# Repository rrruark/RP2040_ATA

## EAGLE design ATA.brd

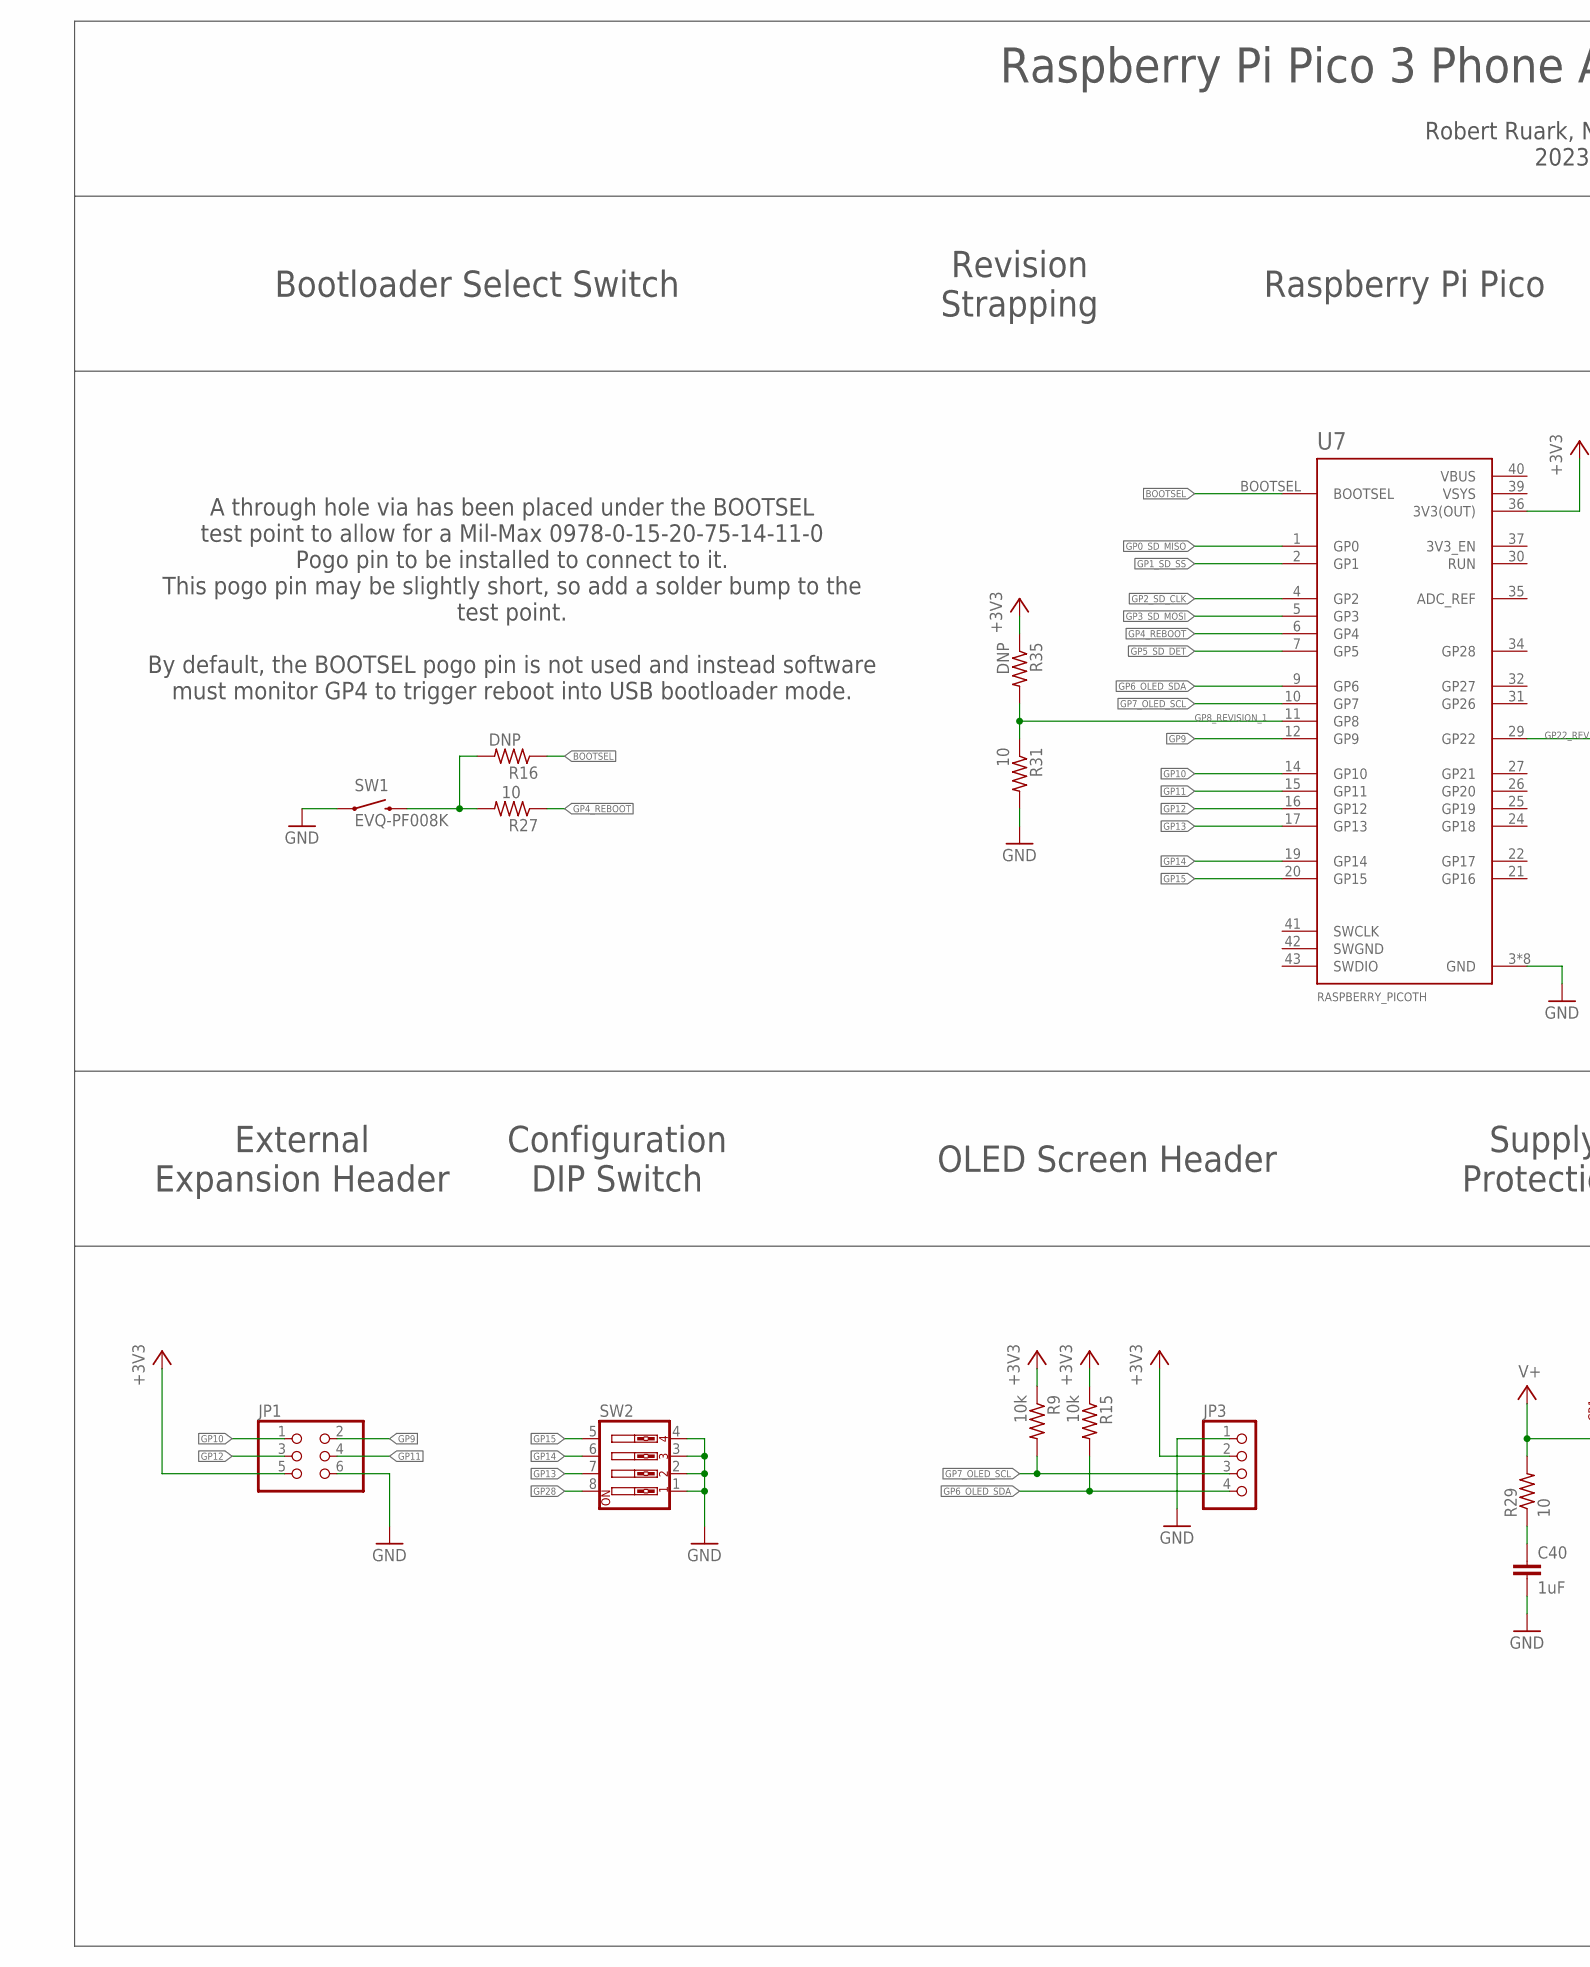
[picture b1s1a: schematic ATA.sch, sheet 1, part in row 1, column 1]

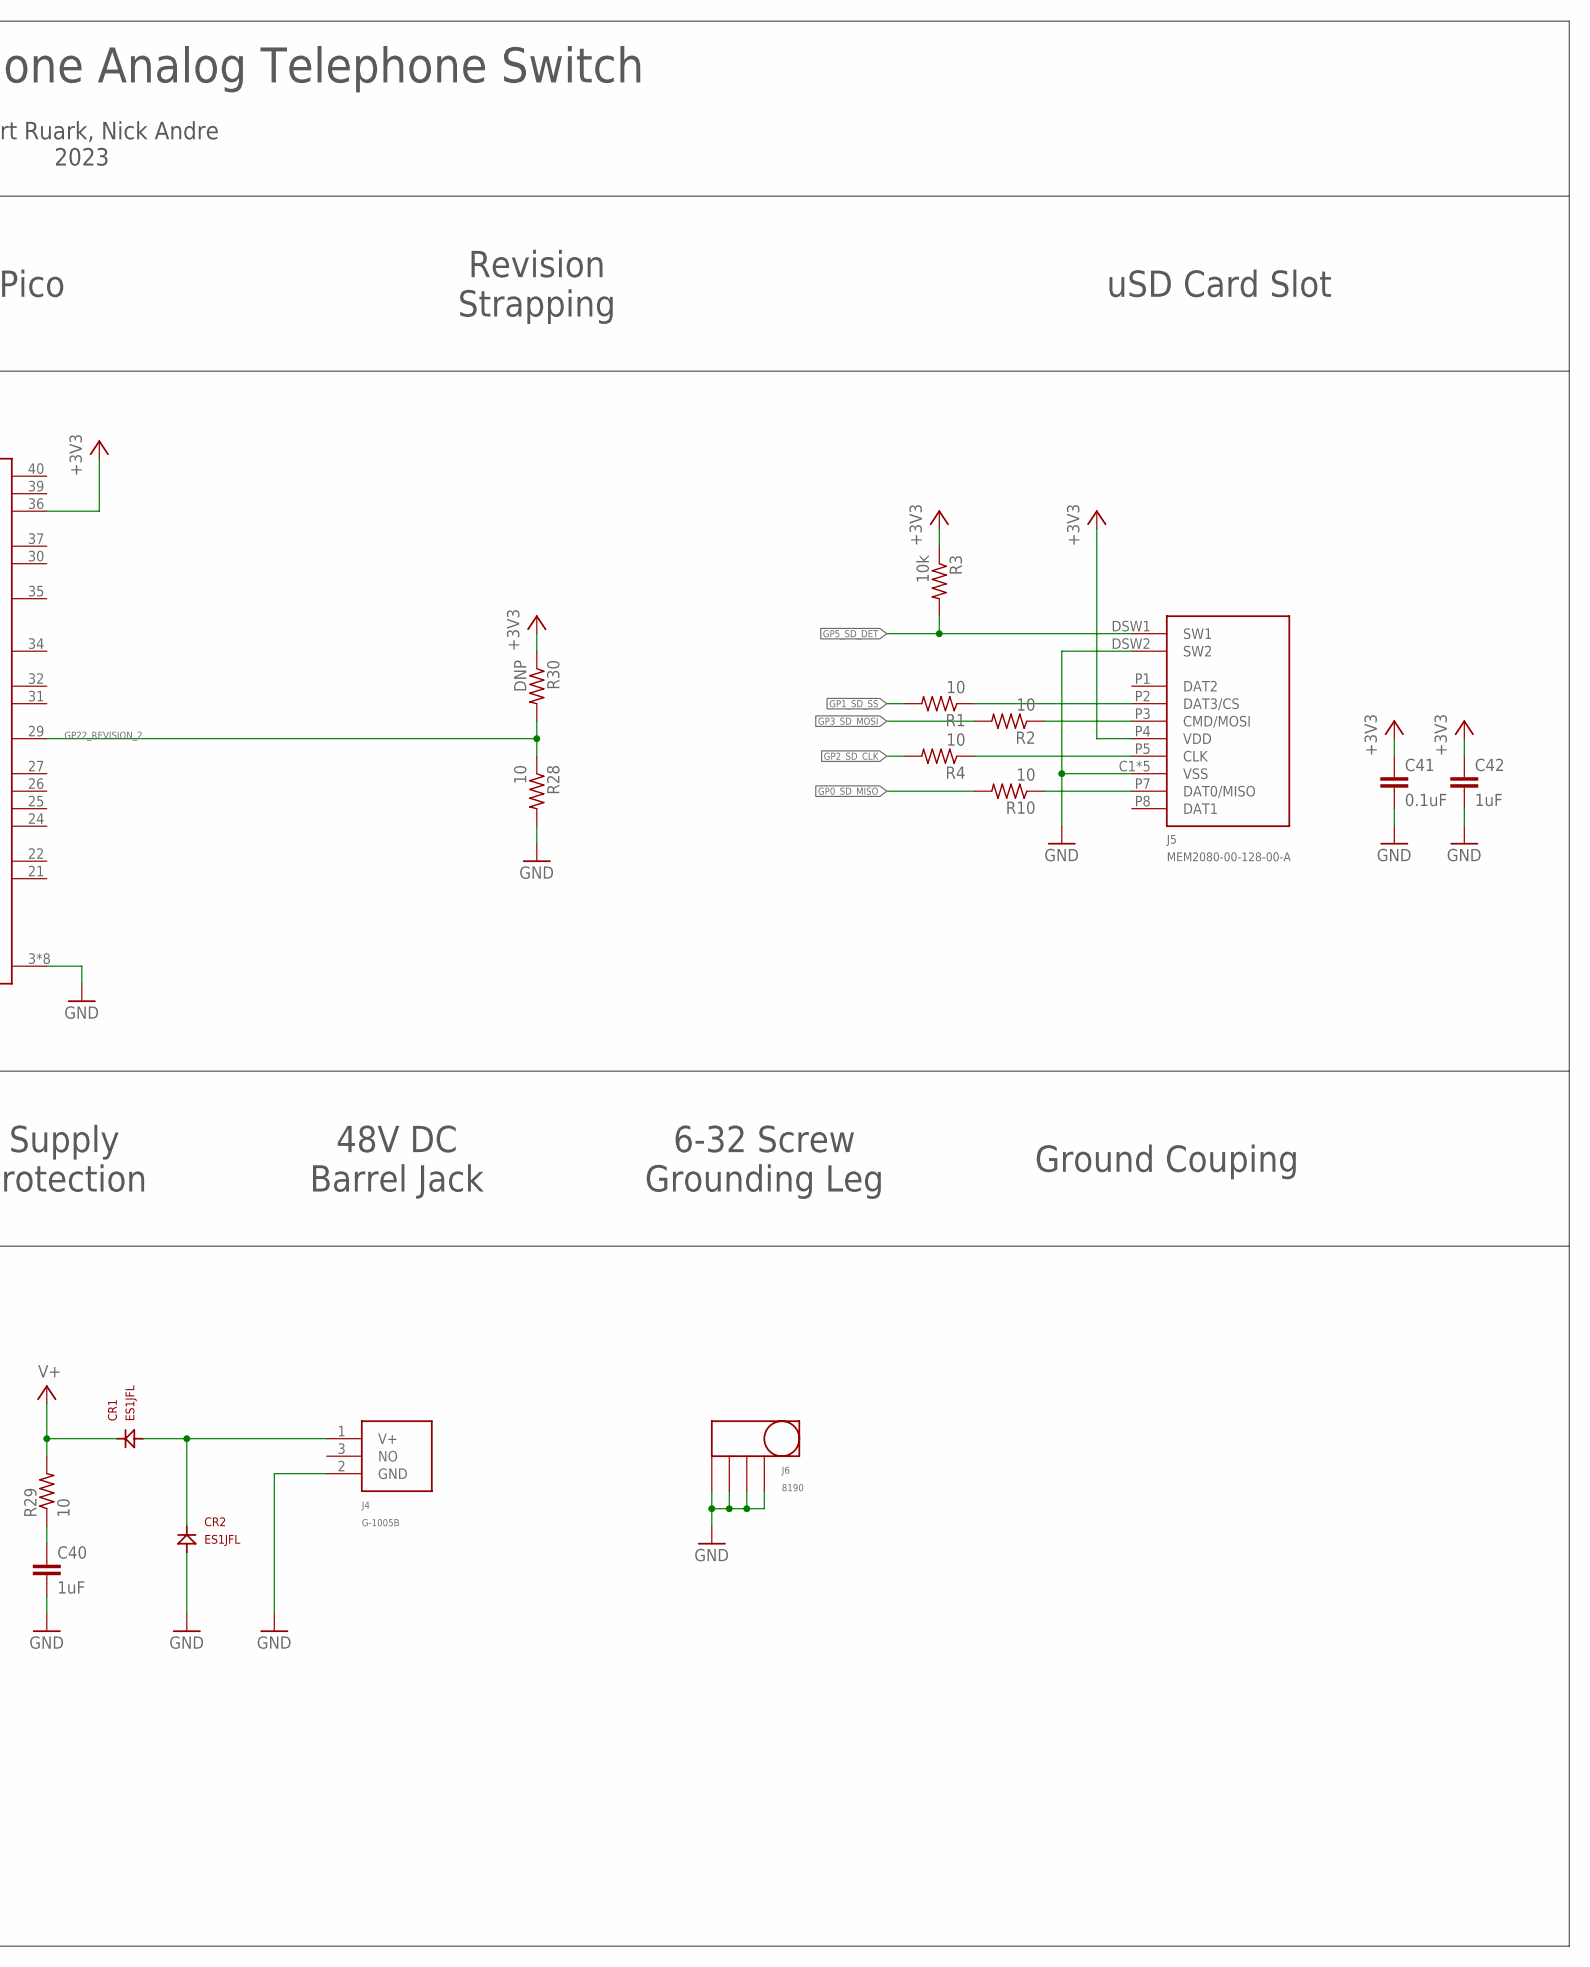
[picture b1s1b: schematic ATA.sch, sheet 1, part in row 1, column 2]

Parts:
C40: 1uF; 1206
C41: 0.1uF; 0603
C42: 1uF; 0805
CR1, CR2: ES1JFL; SOD123(AK)
J4: G-1005B
J5: MEM2080-00-128-00-A; MEM2080
J6: 8190; 7781
JP1: PINHD-2X3/90; 2X03/90
JP3: PINHD-1X4; 1X04
R1, R2, R4, R10, R27, R28, R31: 10; 0603
R3, R9, R15: 10k; 0603
R16, R30, R35: DNP; 0603
R29: 10; 1206
SW1: EVQ-PF008K
SW2: SW_DIP-4; EDG-04
U7: RASPBERRY_PICOTH; PICO-PKG-TH

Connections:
+3V3: C41.1, C42.1, J5.P4 (VDD), JP1.5, JP3.2, R3.1, R9.1, R15.1, R30.1, R35.1, U7.36 (3V3(OUT))
BOOTSEL: R16.1, U7.BOOTSEL
GND: C40.2, C41.2, C42.2, CR2.A, J4.2 (GND), J5.C1 (VSS), J5.C2 (VSS), J5.C3 (VSS), J5.C4 (VSS), J5.DSW2 (SW2), J5.P6 (VSS), J6.P$1, J6.P$2, J6.P$3, J6.P$4, JP1.6, JP3.1, R28.2, R31.2, SW1.S1 (1), SW2.1, SW2.2, SW2.3, SW2.4, U7.3 (GND), U7.8 (GND), U7.13 (GND), U7.18 (GND), U7.23 (GND), U7.28 (GND), U7.33 (GND), U7.38 (GND); also elsewhere on the board
GP0_SD_MISO: R10.2, U7.1 (GP0)
GP1_SD_SS: R1.2, U7.2 (GP1)
GP2_SD_CLK: R4.2, U7.4 (GP2)
GP3_SD_MOSI: R2.2, U7.5 (GP3)
GP4_REBOOT: R27.1, U7.6 (GP4)
GP5_SD_DET: J5.DSW1 (SW1), R3.2, U7.7 (GP5)
GP6_OLED_SDA: JP3.4, R15.2, U7.9 (GP6)
GP7_OLED_SCL: JP3.3, R9.2, U7.10 (GP7)
GP8_REVISION_1: R31.1, R35.2, U7.11 (GP8)
GP9: JP1.2, U7.12 (GP9)
GP10: JP1.1, U7.14 (GP10)
GP11: JP1.4, U7.15 (GP11)
GP12: JP1.3, U7.16 (GP12)
GP13: SW2.7, U7.17 (GP13)
GP14: SW2.6, U7.19 (GP14)
GP15: SW2.5, U7.20 (GP15)
GP22_REVISION_2: R28.1, R30.2, U7.29 (GP22)
GP28: SW2.8
unnamed: R16.2, R27.2, SW1.S2 (2)
unnamed: CR1.A, CR2.K, J4.1 (V+)
unnamed: J5.P5 (CLK), R4.1
unnamed: C40.1, R29.1
unnamed: J5.P7 (DAT0/MISO), R10.1
unnamed: J5.P3 (CMD/MOSI), R2.1
unnamed: J5.P2 (DAT3/CS), R1.1
SWGND: U7.42 (SWGND)
V+: CR1.K, R29.2
VBUS: U7.40 (VBUS)
VSYS: U7.39 (VSYS)

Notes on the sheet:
Raspberry Pi Pico 3 Phone Analog Telephone Switch
Robert Ruark, Nick Andre 2023
Raspberry Pi Pico
Ground Couping
External Expansion Header
OLED Screen Header
48V DC Barrel Jack
6-32 Screw Grounding Leg
A through hole via has been placed under the BOOTSEL test point to allow for a Mil-Max 0978-0-15-20-75-14-11-0 Pogo pin to be installed to connect to it. This pogo pin may be slightly short, so add a solder bump to the test point. By default, the BOOTSEL pogo pin is not used and instead software mu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
Configuration DIP Switch
Supply Protection
Revision Strapping
Bootloader Select Switch
uSD Card Slot

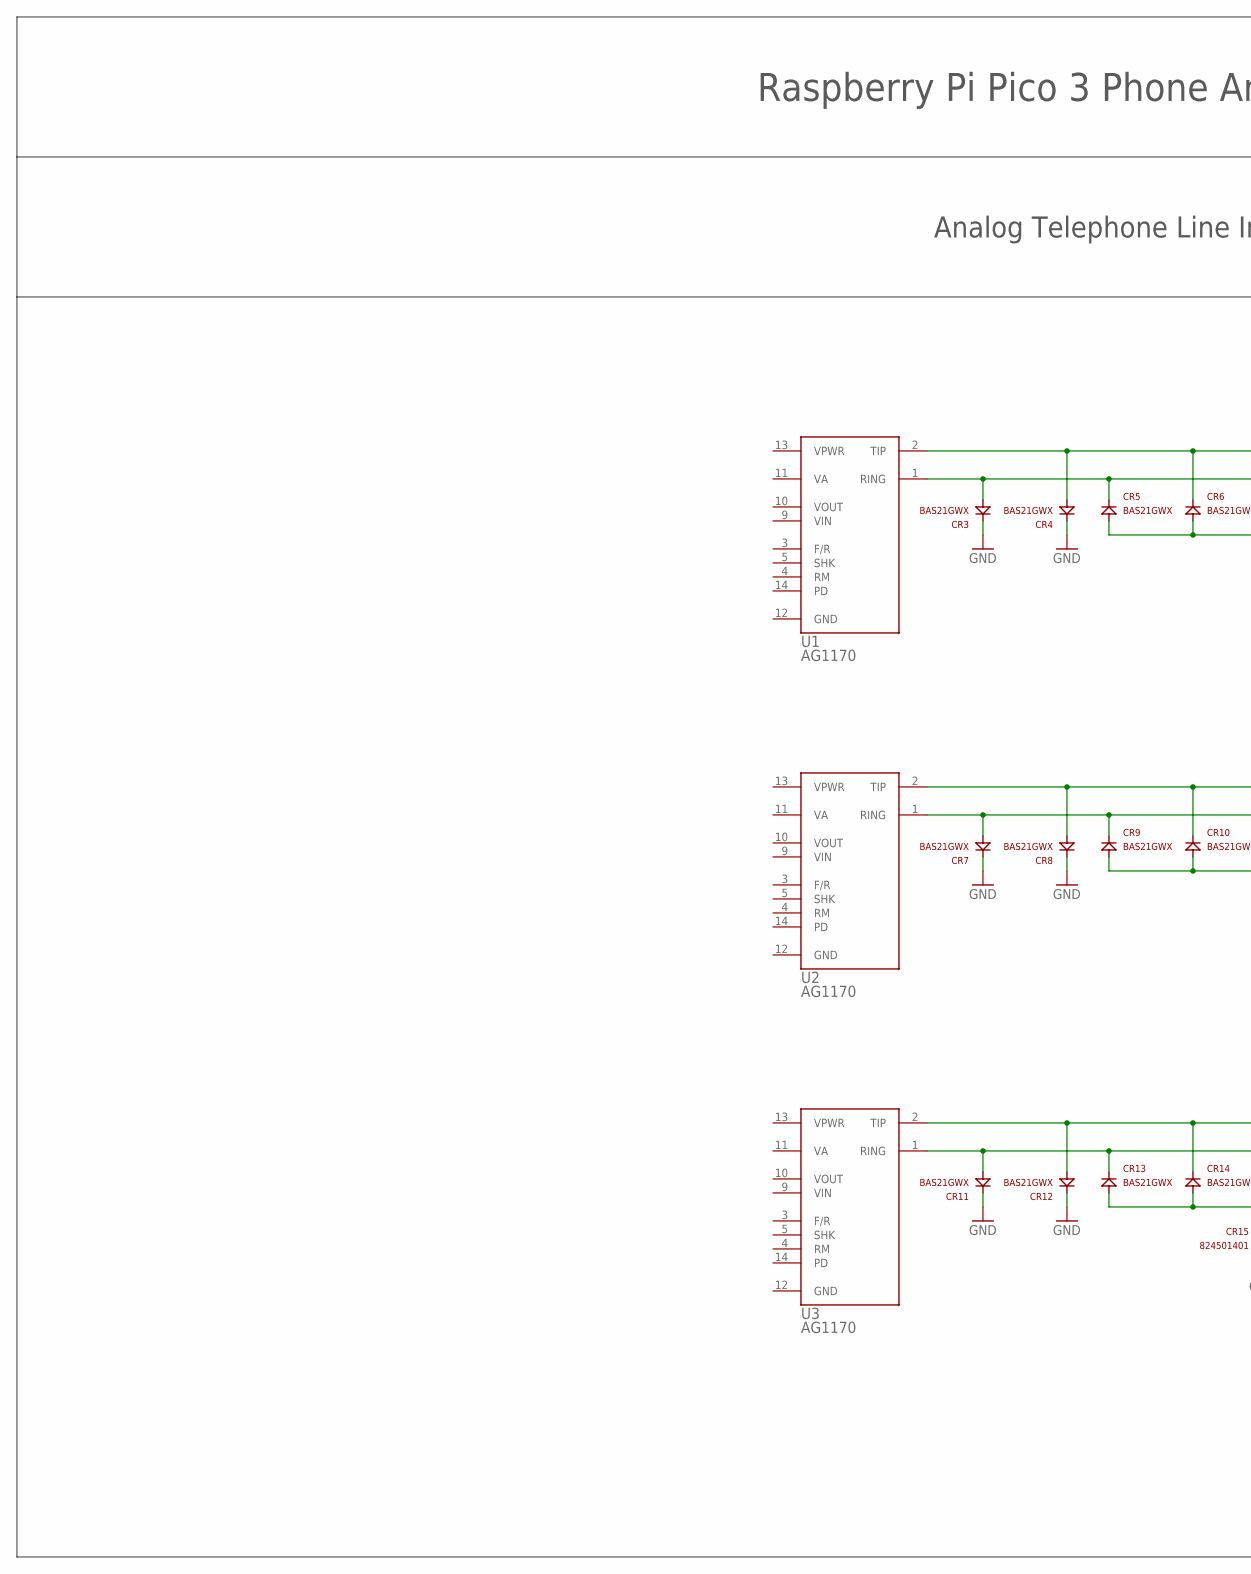
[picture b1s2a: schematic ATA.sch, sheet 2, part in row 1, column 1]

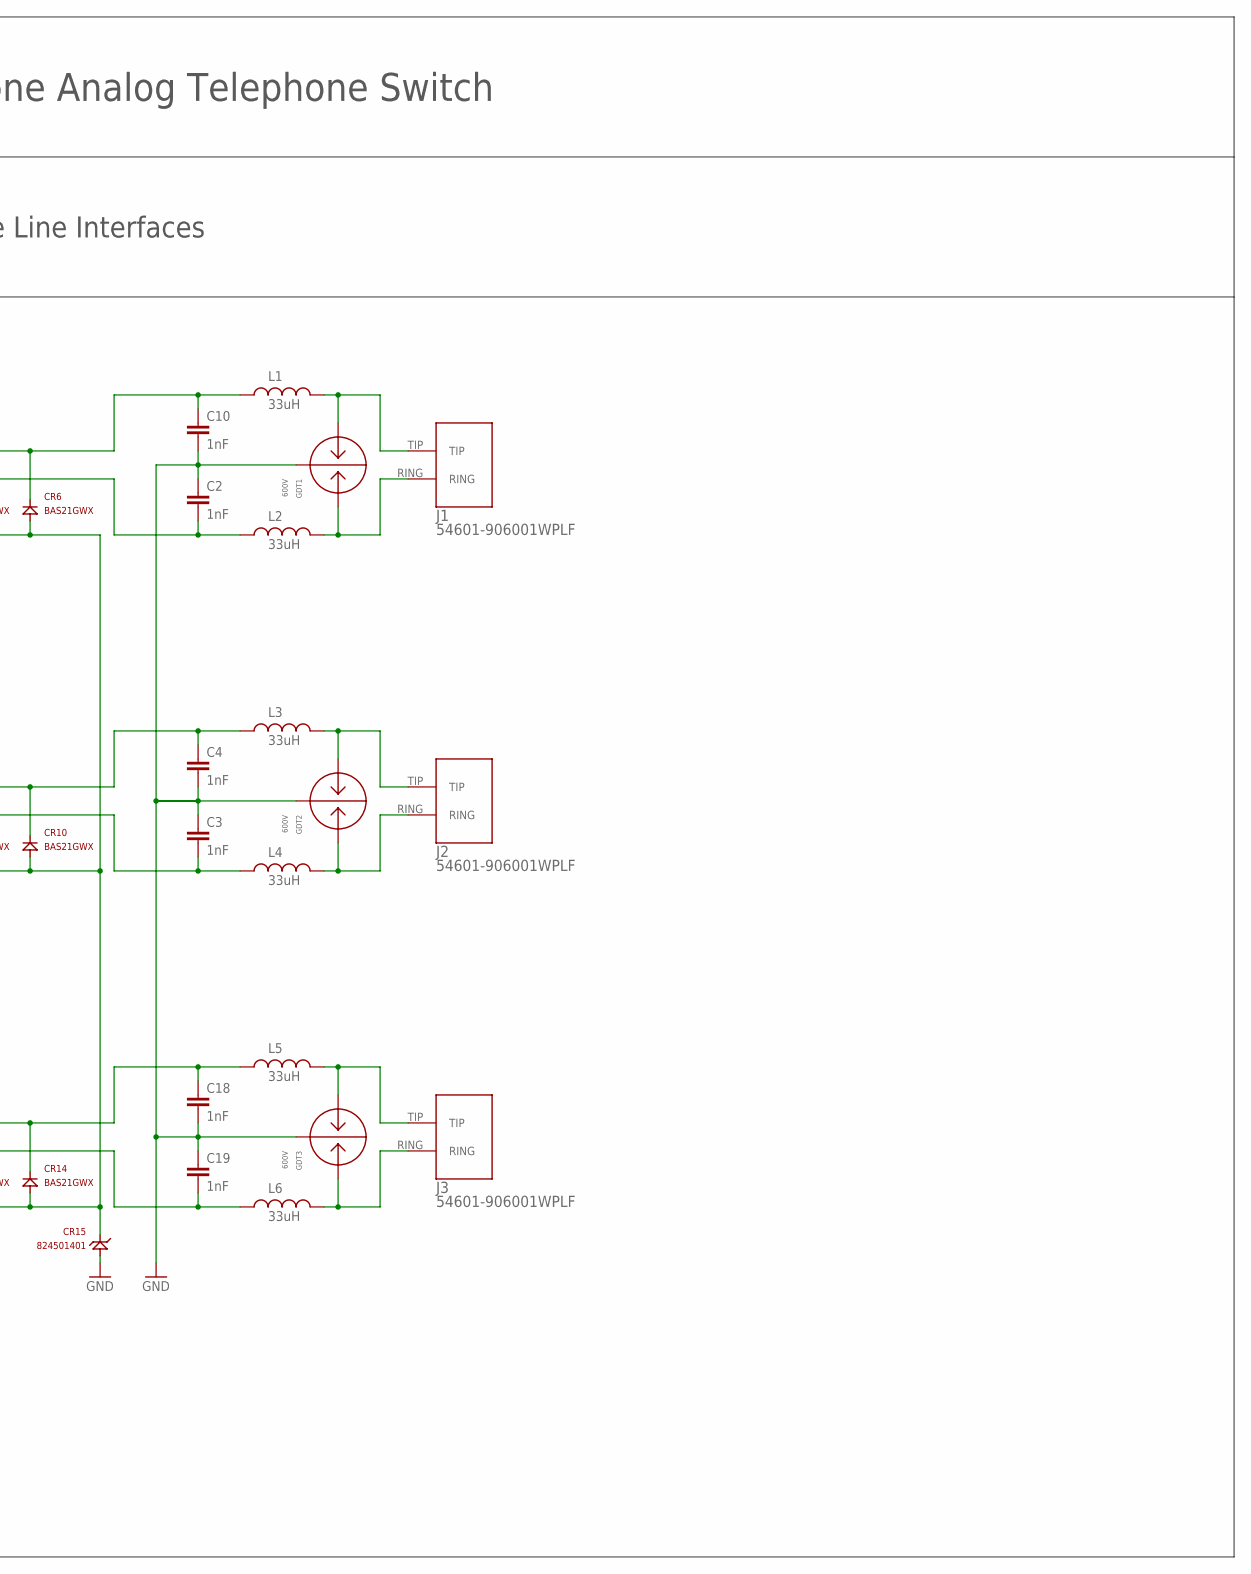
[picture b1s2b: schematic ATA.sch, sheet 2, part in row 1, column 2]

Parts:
C2, C3, C4, C10, C18, C19: 1nF; 0805
CR3, CR4, CR5, CR6, CR7, CR8, CR9, CR10, CR11, CR12, CR13, CR14: BAS21GWX; SOD123
CR15: 824501401; DO-214AC
GDT1, GDT2, GDT3: 600V; 2036_GDT
J1, J2, J3: 54601-906001WPLF
L1, L2, L3, L4, L5, L6: 33uH; SDR0403
U1, U2, U3: AG1170; AG1170S

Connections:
DNVT_1_SWITCH_RX_GREEN: GDT2.L2, J2.RING, L4.2
DNVT_1_SWITCH_RX_GREEN-WHITE: GDT2.L1, J2.TIP, L3.2
DNVT_1_SWITCH_TX_BLUE: GDT1.L2, J1.RING, L2.2
DNVT_1_SWITCH_TX_BLUE-WHITE: GDT1.L1, J1.TIP, L1.2
DNVT_2_SWITCH_TX_ORANGE: GDT3.L2, J3.RING, L6.2
DNVT_2_SWITCH_TX_ORANGE-WHITE: GDT3.L1, J3.TIP, L5.2
GND: C2.1, C3.1, C4.2, C10.2, C18.2, C19.1, CR3.1 (K), CR4.1 (K), CR7.1 (K), CR8.1 (K), CR11.1 (K), CR12.1 (K), CR15.A, GDT1.C, GDT2.C, GDT3.C; also elsewhere on the board
unnamed: C10.1, CR4.2 (A), CR6.1 (K), L1.1, U1.2 (TIP)
unnamed: C2.2, CR3.2 (A), CR5.1 (K), L2.1, U1.1 (RING)
unnamed: C4.1, CR8.2 (A), CR10.1 (K), L3.1, U2.2 (TIP)
unnamed: C3.2, CR7.2 (A), CR9.1 (K), L4.1, U2.1 (RING)
unnamed: CR5.2 (A), CR6.2 (A), CR9.2 (A), CR10.2 (A), CR13.2 (A), CR14.2 (A), CR15.C (K)
unnamed: C18.1, CR12.2 (A), CR14.1 (K), L5.1, U3.2 (TIP)
unnamed: C19.2, CR11.2 (A), CR13.1 (K), L6.1, U3.1 (RING)

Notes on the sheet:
Raspberry Pi Pico 3 Phone Analog Telephone Switch
Analog Telephone Line Interfaces

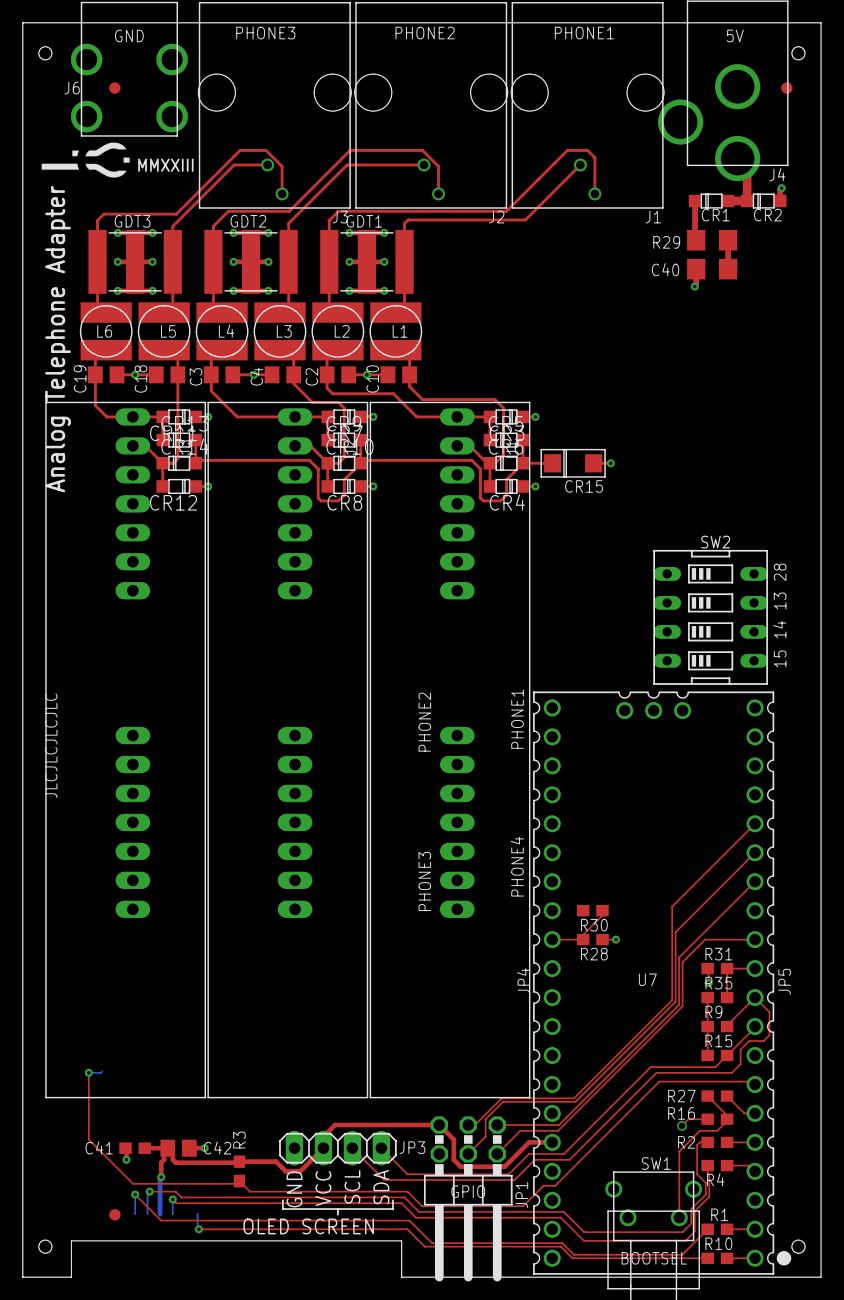
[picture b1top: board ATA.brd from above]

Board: 2 copper layers, 70.0 x 110.0 mm, 61 parts (1 on the bottom side), 41 nets.

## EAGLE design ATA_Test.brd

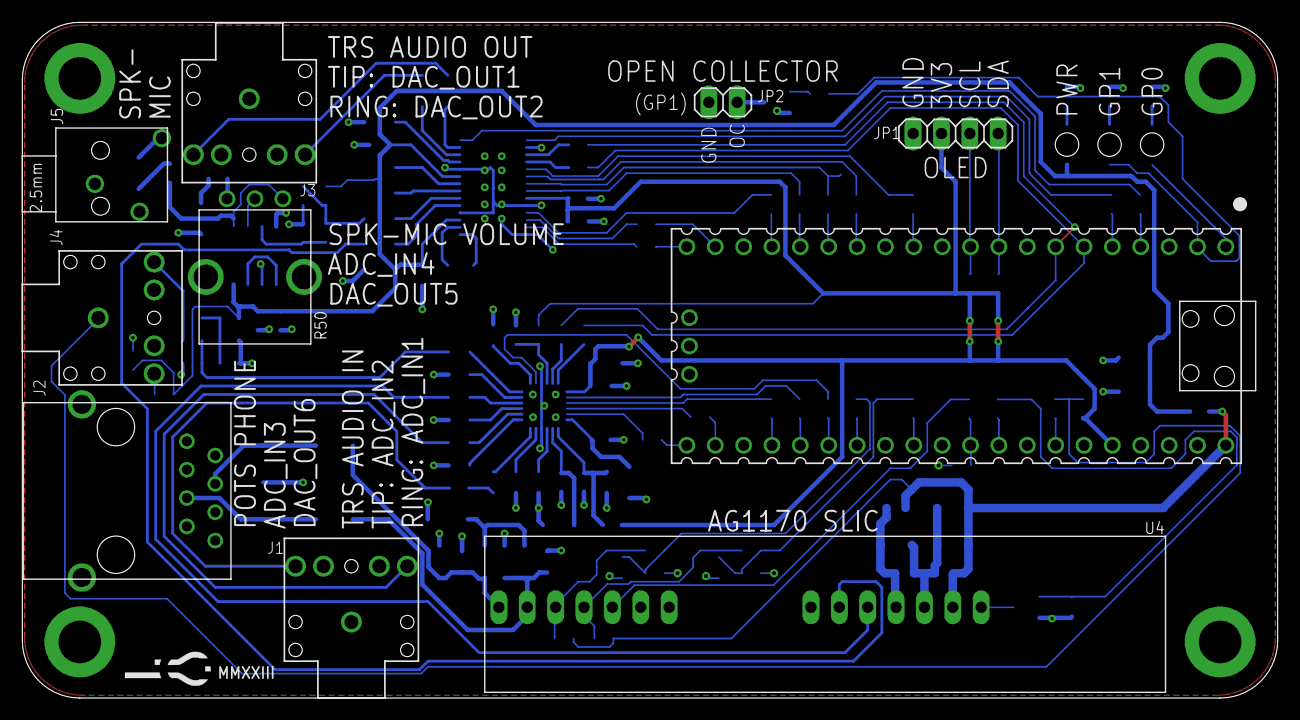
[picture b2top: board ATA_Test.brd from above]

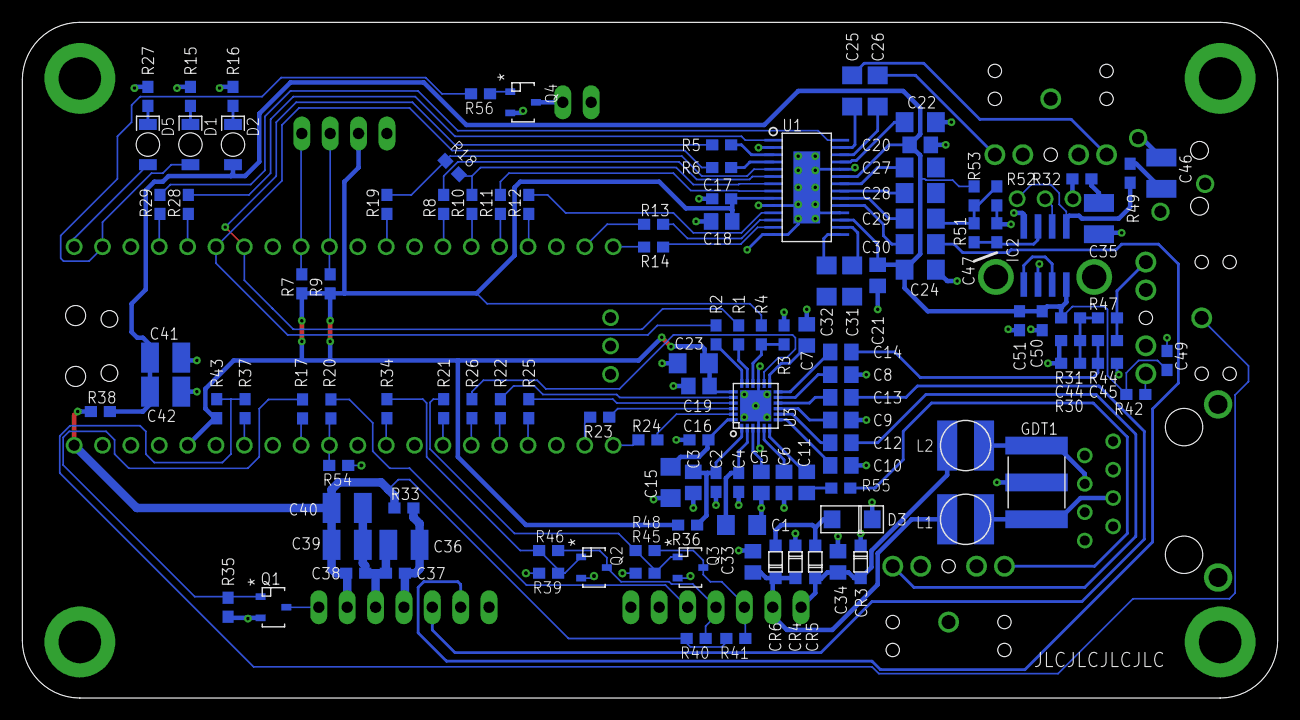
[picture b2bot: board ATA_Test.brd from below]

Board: 2 copper layers, 112.4 x 60.5 mm, 132 parts (122 on the bottom side), 109 nets.

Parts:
C1, C15, C22, C23, C24, C25, C26, C27, C28, C29, C30, C31, C32: 10uF; 1206
C2, C4, C16, C17, C37, C38, C44, C49, C50, C51: 0.1uF; 0603
C3, C5, C6, C7, C8, C9, C10, C11, C12, C13, C14, C18, C19, C20, C21: 1uF; 0805
C33, C34: 1nF; 0805
C35, C36, C39, C40, C41, C42, C46: 100uF; 1210
C45, C47: 1nF; 0603
CR3, CR4, CR5, CR6: BAS21GWX; SOD123
D1, D2, D5: 156120RS75300; 1206_REV
D3: 33V; DO-214AC
GDT1: 600V; 2036_GDT
IC2: LM833D; SO08
J1, J3, J4: SJ1-3523N
J2: A-2004-2-4-LPS-N-R
J5: SJ-2509N; 2.5MM_TRS
JP1: 1X04
JP2: 1X02
L1, L2: 33uH; SDR0403
Q1, Q4: MMBT3904; SOT23-3_CENTERED
Q2, Q3: DNP; SOT23-3_CENTERED
R1, R2, R4, R5, R6, R8, R10, R11, R12, R13, R14, R19, R21, R22, R23, R24, R25, R26, R28, R29, R33, R34, R36, R37, R38, R46, R48, R49, R55: 10; 0603
R3, R18, R30, R39, R40, R41, R45: DNP; 0603
R7, R9, R15, R16, R17, R27, R35, R47, R52, R53, R56: 10k; 0603
R20, R31, R42, R43: 1k; 0603
R32, R44, R51: 100; 0603
R50: 10k; PTV09
R54: 2k; 0603
U1: PCM1681PWPR; TSSOP28-POWER
U2: RASPBERRY_PICOTH; PICO-PKG-TH
U3: TLV320ADC3140; QFN24-55
U4: AG1170; AG1170S

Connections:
+3V3: C17.1, C18.1, C19.1, C23.1, JP1.2, R4.1, R7.1, R9.1, R36.2, R43.2, U1.9, U2.36, U3.19
+5V: C20.1, C21.1, C24.1, C41.2, C42.2, C49.1, C50.1, C51.1, D2.A, IC2.8, R31.2, R38.2, R42.2, R53.2, U1.17, U1.23
ADC_AREG: C1.1, C4.1, U3.2
ADC_BCLK: R23.1, U3.22
ADC_FSYNC: R24.1, U3.23
ADC_GPIO1: R22.1, U3.20
ADC_IN1: J1.3, R55.2
ADC_IN2: C12.2, J1.2
ADC_IN3: C13.2, U4.10
ADC_IN4: C14.2, C45.1, R44.1
ADC_MICBIAS: C6.1, U3.5
ADC_SDOUT: R25.1, U3.21
ADC_SHDNZ: R26.1, U3.14
ADC_VREF: C5.1, U3.3
DAC_BCK: R10.2, R18.1, U1.7
DAC_DATA1: R8.2, U1.6
DAC_DATA2: R12.2, U1.11
DAC_DATA3: R13.2, U1.12
DAC_DATA4: R14.2, U1.13
DAC_LRCK: R11.2, U1.8
DAC_OUT1: C25.2, J3.2
DAC_OUT2: C26.2, J3.3
DAC_OUT5: C29.2, R51.1, R52.2, R53.1
DAC_OUT6: C30.2, U4.9
DAC_SCK: R18.2, R19.2, U1.5
DAC_ZR1: R28.2, U1.1
DAC_ZR2: R29.2, U1.28
DNVT_1_SWITCH_TX_BLUE: GDT1.L2, J2.4, L2.2
DNVT_1_SWITCH_TX_BLUE-WHITE: GDT1.L1, J2.5, L1.2
F/R: Q3.3, R41.2, R48.2, U4.3
F/R_R: Q3.1, R21.1, R45.1, R48.1
GND: C1.2, C2.2, C3.2, C4.2, C5.2, C6.2, C7.2, C8.2, C9.2, C10.2, C15.2, C16.2, C17.2, C18.2, C19.2, C20.2, C21.2, C22.2, C23.2, C24.2, C33.2, C34.1, C35.1, C36.1, C37.2, C38.2, C39.1, C40.1, C41.1, C42.1, C44.2, C45.2, C47.2, C49.2, C50.2, C51.2, CR3.1, CR4.1, D3.C, GDT1.C, IC2.4, IC2.6, J1.1, J2.S1, J2.S2, J3.1, J5.R, J5.S, JP1.1, JP2.2, Q1.2, Q2.2, Q3.2, Q4.2, R3.1, R15.2, R16.2, R27.2, R30.1, R35.2, R39.2, R45.2, R52.1, R54.1, U1.2, U1.10, U1.14, U1.18, U1.24, U1.EP, U2.3, U2.8, U2.13, U2.18, U2.23, U2.28, U2.33, U2.38, U3.4, U3.15, U3.EP, U4.12
GP4_I2C0_SDA: R2.1, R6.2, U2.6
GP5_I2C0_SCL: R1.1, R5.2, U2.7
GP6_I2C1_SDA: JP1.4, R7.2, U2.9
GP7_I2C1_SCL: JP1.3, R9.2, U2.10
unnamed: C7.1, U3.13
unnamed: C8.1, U3.11
unnamed: C9.1, U3.9
unnamed: C10.1, U3.7
unnamed: C14.1, U3.12
unnamed: C13.1, U3.10
unnamed: C12.1, U3.8
unnamed: C11.1, U3.6
unnamed: R1.2, U3.17
unnamed: C22.1, U1.25
unnamed: C15.1, C16.1, U3.24
unnamed: R3.2, R4.2, U3.16
unnamed: C26.1, U1.26
unnamed: C25.1, U1.27
unnamed: R2.2, U3.18
unnamed: R24.2, U2.21
unnamed: R23.2, U2.22
unnamed: D1.K, R15.1
unnamed: R5.1, U1.3
unnamed: D2.K, R16.1
unnamed: R25.2, U2.24
unnamed: R22.2, U2.25
unnamed: R21.2, U2.27
unnamed: R26.2, U2.26
unnamed: R17.2, U2.32
unnamed: R20.2, R54.2, U2.31
unnamed: D5.K, R27.1
unnamed: JP2.1, Q4.3
unnamed: D1.A, R56.2, U2.2
unnamed: D5.A, U2.1
unnamed: R19.1, U2.12
unnamed: C33.1, CR4.2, CR6.1, L1.1, U4.2
unnamed: C34.2, CR3.2, CR5.1, L2.1, U4.1
unnamed: CR5.2, CR6.2, D3.A
unnamed: R28.1, U2.5
unnamed: R8.1, U2.14
unnamed: R10.1, U2.15
unnamed: R11.1, U2.16
unnamed: R12.1, U2.17
unnamed: R13.1, U2.19
unnamed: R14.1, U2.20
unnamed: R6.1, U1.4
unnamed: C27.1, U1.22
unnamed: C28.1, U1.21
unnamed: C29.1, U1.20
unnamed: C35.2, R32.2
unnamed: C31.1, U1.16
unnamed: C32.1, U1.15
unnamed: C30.1, U1.19
unnamed: R32.1, R50.3
unnamed: R29.1, U2.4
unnamed: Q1.3, U4.14
unnamed: C36.2, C37.1, R33.2, U4.11
unnamed: R37.2, U2.34
unnamed: R34.2, U2.29
unnamed: C11.2, R55.1
unnamed: Q4.1, R56.1
unnamed: J4.2, R42.1
unnamed: J4.3, R44.2, R47.1
unnamed: C44.1, R30.2, R31.1, R47.2
unnamed: C46.2, J5.T
unnamed: IC2.5, IC2.7
unnamed: IC2.1, R49.1, R50.1
unnamed: C46.1, R49.2
unnamed: IC2.2, R50.2
unnamed: C47.1, IC2.3, R51.2
PD: Q1.1, R17.1, R35.1
PTT: J4.1, R37.1, R43.1
RM: Q2.3, R40.2, R46.2, U4.4
RM_R: Q2.1, R34.1, R39.1, R46.1
SHK: R20.1, U4.5
V+: C38.1, C39.2, C40.2, R33.1, R38.1, R40.1, R41.1, U2.40, U4.13
VCC: C2.1, C3.1, R36.1, U3.1

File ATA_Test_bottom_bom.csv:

Comment,Designator,Footprint,LCSC Part #
0.1uF,C2 C4 C16 C17 C37 C38 C44 C49 C50 C51,0603,
1k,R20 R31 R42 R43,0603,
1nF,C33 C34,0805,
1nF,C45 C47,0603,
1uF,C3 C5 C6 C7 C8 C9 C10 C11 C12 C13 C14 C18 C19 C20 C21,0805,
2k,R54,0603,
10,R1 R2 R4 R5 R6 R8 R10 R11 R12 R13 R14 R19 R21 R22 R23 R24 R25 R26 R28 R29 R33 R34 R36 R37 R38 R46 R48 R49 R55,0603,
10k,R7 R9 R15 R16 R17 R27 R35 R47 R52 R53 R56,0603,
10uF,C1 C15 C22 C23 C24 C25 C26 C27 C28 C29 C30 C31 C32,1206,
33V,D3,DO-214AC,
33uH,L1 L2,SDR0403,
100,R32 R44 R51,0603,
100uF,C35 C36 C39 C40 C41 C42 C46,1210,
600V,GDT1,2036_GDT,
156120RS75300,D1 D2 D5,1206_REV,
BAS21GWX,CR3 CR4 CR5 CR6,SOD123,
DNP,Q2 Q3,SOT23-3_CENTERED,
DNP,R3 R18 R30 R39 R40 R41 R45,0603,
LM833D,IC2,SO08,
MMBT3904,Q1 Q4,SOT23-3_CENTERED,
PCM1681PWPR,U1,TSSOP28-POWER,
TLV320ADC3140,U3,QFN24-55,

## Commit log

2023-03-25 Initial Commit
    Box and line interfaces. Connections to RP2040 still need to be made.
2023-04-01 Draft Test Board
2023-05-06 adding pdf
2023-05-07 Added arduino test code
